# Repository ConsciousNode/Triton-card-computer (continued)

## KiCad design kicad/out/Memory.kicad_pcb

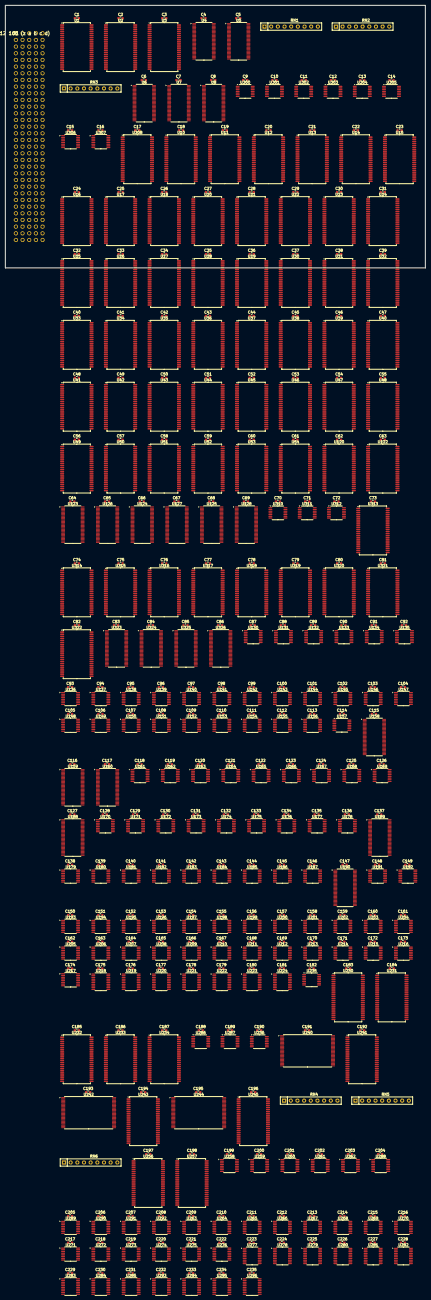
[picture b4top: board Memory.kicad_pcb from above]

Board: 4 copper layers, 160.0 x 100.0 mm, 477 parts (0 on the bottom side), 1061 nets, no tracks yet.

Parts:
C1, C2, C3, C4, C5, C6, C7, C8, C9, C10, C11, C12, C13, C14, C15, C16, C17, C18, C19, C20, C21, C22, C23, C24, C25, C26, C27, C28, C29, C30, C31, C32, C33, C34, C35, C36, C37, C38, C39, C40, C41, C42, C43, C44, C45, C46, C47, C48, C49, C50, C51, C52, C53, C54, C55, C56, C57, C58, C59, C60, C61, C62, C63, C64, C65, C66, C67, C68, C69, C70, C71, C72, C73, C74, C75, C76, C77, C78, C79, C80, C81, C82, C83, C84, C85, C86, C87, C88, C89, C90, C91, C92, C93, C94, C95, C96, C97, C98, C99, C100, C101, C102, C103, C104, C105, C106, C107, C108, C109, C110, C111, C112, C113, C114, C115, C116, C117, C118, C119, C120, C121, C122, C123, C124, C125, C126, C127, C128, C129, C130, C131, C132, C133, C134, C135, C136, C137, C138, C139, C140, C141, C142, C143, C144, C145, C146, C147, C148, C149, C150, C151, C152, C153, C154, C155, C156, C157, C158, C159, C160, C161, C162, C163, C164, C165, C166, C167, C168, C169, C170, C171, C172, C173, C174, C175, C176, C177, C178, C179, C180, C181, C182, C183, C184, C185, C186, C187, C188, C189, C190, C191, C192, C193, C194, C195, C196, C197, C198, C199, C200, C201, C202, C203, C204, C205, C206, C207, C208, C209, C210, C211, C212, C213, C214, C215, C216, C217, C218, C219, C220, C221, C222, C223, C224, C225, C226, C227, C228, C229, C230, C231, C232, C233, C234, C235: 100n; C_0603_1608Metric
J1: DIN41612 160 (z a b c d)
RN1, RN2, RN3: RPACK8; R_Array_SIP9
RN4, RN5, RN6: RPACK8G; R_Array_SIP9
U1, U2, U3, U10, U11, U12, U13, U14, U15, U16, U17, U18, U20, U21, U22, U23, U24, U25, U26, U27, U28, U29, U30, U31, U32, U33, U34, U35, U36, U37, U38, U39, U40, U41, U42, U43, U44, U45, U46, U47, U48, U49, U50, U51, U52, U53, U54, U120, U122, U230, U231, U232, U233, U234, U308, U313, U314, U315, U316, U317, U318, U319, U320, U321, U322: IS61WV5128; TSOP-II-44_10.16x18.41mm_P0.8mm
U4, U5, U6, U7, U8, U123, U124, U125, U126, U127, U128, U158, U159, U160, U188, U189, U190, U323, U324, U325, U326: ALVCH16823; TSSOP-56_6.1x14mm_P0.5mm
U130, U131, U132, U133, U134, U135, U136, U137, U138, U139, U140, U141, U142, U143, U144, U145, U146, U147, U148, U149, U150, U151, U152, U153, U154, U155, U156, U161, U162, U163, U164, U165, U166, U167, U168, U169, U170, U171, U172, U173, U174, U175, U176, U177, U178, U179, U180, U181, U182, U183, U184, U185, U186, U187, U268, U269, U270, U271, U272, U273, U274, U275, U276: LVC153; TSSOP-16_4.4x5mm_P0.65mm
U157, U235: LVC04; TSSOP-14_4.4x5mm_P0.65mm
U191, U192, U193, U194, U195, U196, U197, U198, U199, U200, U201, U202, U203, U204, U205, U206, U207, U208, U209, U210, U211, U212, U213, U214, U215, U216, U217: CBTLV3253; TSSOP-16_4.4x5mm_P0.65mm
U218, U219, U220, U221, U222, U223, U224, U277, U278, U279, U280, U281, U282, U283, U293, U294, U295, U296: LVC245; TSSOP-20_4.4x6.5mm_P0.65mm
U236, U287: LVC32; TSSOP-14_4.4x5mm_P0.65mm
U240, U242, U244: IS61WV204816; TSOP-I-48_18.4x12mm_P0.5mm
U241, U243, U245: IS61WV20488; TSOP-II-44_10.16x18.41mm_P0.8mm
U256, U257: IS61WV51216; TSOP-II-44_10.16x18.41mm_P0.8mm
U258, U259, U260, U261, U262: CBTLV3257; TSSOP-16_4.4x5mm_P0.65mm
U263, U264, U265, U266, U267, U288, U289, U290, U291, U292, U306, U307: LVC157; TSSOP-16_4.4x5mm_P0.65mm
U284, U285: LVC574; TSSOP-20_4.4x6.5mm_P0.65mm
U286: LVC08; TSSOP-14_4.4x5mm_P0.65mm
U300, U301, U302, U303, U304, U305, U310, U311, U312: LVC11; TSSOP-14_4.4x5mm_P0.65mm

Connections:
+3V3: C1.1, C2.1, C3.1, C4.1, C5.1, C6.1, C7.1, C8.1, C9.1, C10.1, C11.1, C12.1, C13.1, C14.1, C15.1, C16.1, C17.1, C18.1, C19.1, C20.1, C21.1, C22.1, C23.1, C24.1, C25.1, C26.1, C27.1, C28.1, C29.1, C30.1, C31.1, C32.1, C33.1, C34.1, C35.1, C36.1, C37.1, C38.1, C39.1, C40.1, C41.1, C42.1, C43.1, C44.1, C45.1, C46.1, C47.1, C48.1, C49.1, C50.1, C51.1, C52.1, C53.1, C54.1, C55.1, C56.1, C57.1, C58.1, C59.1, C60.1, C61.1, C62.1, C63.1, C64.1, C65.1, C66.1, C67.1, C68.1, C69.1, C70.1, C71.1, C72.1, C73.1, C74.1, C75.1, C76.1, C77.1, C78.1, C79.1, C80.1, C81.1, C82.1, C83.1, C84.1, C85.1, C86.1, C87.1, C88.1, C89.1, C90.1, C91.1, C92.1, C93.1, C94.1, C95.1, C96.1, C97.1, C98.1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
+5V: J1.z8, J1.z16, J1.z24, J1.z32
/CE0: U234.9, U240.7, U241.8
/CE1: U234.10, U242.7, U243.8
/CE2: U234.13, U244.7, U245.8
/FALD: U157.2, U158.30, U158.55, U159.30, U159.55, U160.30, U160.55
/RWE: U236.6, U240.18, U241.15, U242.18, U243.15, U244.18, U245.15
/SWR: U235.11, U286.2, U286.5, U293.19, U294.19, U295.19, U296.19
/UBLD: U122.9, U123.30, U123.55, U124.30, U124.55, U125.30, U125.55
/ULLD: U122.10, U126.30, U126.55, U127.30, U127.55, U128.30, U128.55, U323.30, U323.55, U324.30, U324.55, U325.30, U325.55, U326.30, U326.55
/VSWE: U257.17, U286.6
/VWE: U235.3, U236.8, U282.19, U283.19, U286.1, U286.4
/VXWE: U256.17, U286.3
/WA: U236.3, U236.9, U236.12
/WAS: U236.4, U236.11
/WSTB: J1.d1, U236.13
ABORT: J1.c15, U6.30, U6.55, U7.30, U7.55, U8.30, U8.55, U120.9, U122.18, U157.1, U188.30, U188.55, U189.30, U189.55, U190.30, U190.55, U236.2
BADADDR: J1.d2, U120.31
CLK: J1.c10, U4.29, U4.56, U5.29, U5.56, U6.29, U6.56, U7.29, U7.56, U8.29, U8.56, U123.29, U123.56, U124.29, U124.56, U125.29, U125.56, U126.29, U126.56, U127.29, U127.56, U128.29, U128.56, U158.29, U158.56, U159.29, U159.56, U160.29, U160.56, U188.29, U188.56, U189.29, U189.56, U190.29, U190.56, U323.29, U323.56, U324.29, U324.56, U325.29, U325.56, U326.29, U326.56
CSD0: U1.9, U4.54
CSD1: U1.10, U4.52
CSD2: U1.13, U4.51
CSD3: U1.14, U4.49
CSD4: U1.31, U4.48
CSD5: U1.32, U4.47
CSD6: U1.35, U4.45
CSD7: U1.36, U4.44
CSD8: U2.9, U4.43
CSD9: U2.10, U4.42
CSD10: U2.13, U4.41
CSD11: U2.14, U4.40
CSD12: U2.31, U4.38
CSD13: U2.32, U4.37
CSD14: U2.35, U4.36
CSD15: U2.36, U4.34
CSD16: U3.9, U4.33
CSD17: U3.10, U4.31
CSD18: U3.13, U5.54
CSD19: U3.14, U5.52
CSD20: U3.31, U5.51
CSD21: U3.32, U5.49
CW_/MBUSOE: RN3.3, U4.26, U218.19, U219.19, U220.19, U221.19, U222.19, U223.19, U224.19
CW_/MWR: RN3.5, U5.5, U235.1, U236.1, U277.19, U278.19, U279.19, U280.19, U281.19
CW_BS0_0: RN2.5, U4.17, U191.14, U192.14, U193.14, U194.14, U195.14, U196.14, U197.14, U198.14, U199.14
CW_BS0_1: RN2.6, U4.19, U191.2, U192.2, U193.2, U194.2, U195.2, U196.2, U197.2, U198.2, U199.2
CW_BS1_0: RN2.7, U4.20, U200.14, U201.14, U202.14, U203.14, U204.14, U205.14, U206.14, U207.14, U208.14
CW_BS1_1: RN2.8, U4.21, U200.2, U201.2, U202.2, U203.2, U204.2, U205.2, U206.2, U207.2, U208.2
CW_BS2_0: RN2.9, U4.23, U209.14, U210.14, U211.14, U212.14, U213.14, U214.14, U215.14, U216.14, U217.14
CW_BS2_1: RN3.2, U4.24, U209.2, U210.2, U211.2, U212.2, U213.2, U214.2, U215.2, U216.2, U217.2
CW_MARC: RN1.4, U4.6, U10.28, U308.19
CW_MK0: RN2.3, U4.15, U120.6
CW_MK1: RN2.4, U4.16, U120.7
CW_MOP0: RN1.2, U4.3, U10.29, U11.29, U12.29, U13.29, U14.29, U15.29, U16.29, U17.29, U18.29
CW_MOP1: RN1.3, U4.5, U10.30, U11.30, U12.30, U13.30, U14.30, U15.30, U16.30, U17.30, U18.30, U306.1, U307.1
CW_MS0_0: RN1.5, U4.8, U161.14, U162.14, U163.14, U164.14, U165.14, U166.14, U167.14, U168.14, U169.14
CW_MS0_1: RN1.6, U4.9, U161.2, U162.2, U163.2, U164.2, U165.2, U166.2, U167.2, U168.2, U169.2
CW_MS1_0: RN1.7, U4.10, U170.14, U171.14, U172.14, U173.14, U174.14, U175.14, U176.14, U177.14, U178.14
CW_MS1_1: RN1.8, U4.12, U170.2, U171.2, U172.2, U173.2, U174.2, U175.2, U176.2, U177.2, U178.2
CW_MS2_0: RN1.9, U4.13, U179.14, U180.14, U181.14, U182.14, U183.14, U184.14, U185.14, U186.14, U187.14
CW_MS2_1: RN2.2, U4.14, U179.2, U180.2, U181.2, U182.2, U183.2, U184.2, U185.2, U186.2, U187.2
CW_RFWR: RN3.4, U5.3, U122.16
CW_WL0: RN3.6, U5.6, U268.14, U269.14, U270.14, U271.14, U272.14, U273.14, U274.14, U275.14, U276.14
CW_WL1: RN3.7, U5.8, U268.2, U269.2, U270.2, U271.2, U272.2, U273.2, U274.2, U275.2, U276.2
D0+: J1.a1, U10.17, U123.54, U126.54, U161.4, U161.5, U170.4, U179.4, U218.18, U302.9, U313.3, U314.3
D0-: J1.a2, U10.18, U123.52, U126.52, U161.11, U161.12, U170.12, U179.12, U218.17, U313.4, U314.4
D1+: J1.a3, U10.19, U123.51, U126.51, U162.4, U162.5, U171.4, U180.4, U218.16, U302.10, U313.5, U314.5
D1-: J1.a4, U10.20, U123.49, U126.49, U162.11, U162.12, U171.12, U180.12, U218.15, U313.6, U314.6
D2+: J1.a5, U10.26, U123.48, U126.48, U163.4, U163.5, U172.4, U181.4, U218.14, U302.11, U313.7, U314.7
D2-: J1.a6, U10.27, U123.47, U126.47, U163.11, U163.12, U172.12, U181.12, U218.13, U313.16, U314.16
D3+: J1.a7, U11.17, U123.45, U126.45, U164.4, U164.5, U173.4, U182.4, U218.12, U303.1, U315.3
D3-: J1.a9, U11.18, U123.44, U126.44, U164.11, U164.12, U173.12, U182.12, U218.11, U310.1, U315.4
D4+: J1.a10, U11.19, U123.43, U126.43, U165.4, U165.5, U174.4, U183.4, U219.18, U303.2, U315.5
D4-: J1.a11, U11.20, U123.42, U126.42, U165.11, U165.12, U174.12, U183.12, U219.17, U310.2, U315.6
D5+: J1.a12, U11.26, U123.41, U126.41, U166.4, U166.5, U175.4, U184.4, U219.16, U303.13, U315.7
D5-: J1.a13, U11.27, U123.40, U126.40, U166.11, U166.12, U175.12, U184.12, U219.15, U310.13, U315.16
D6+: J1.a14, U12.17, U123.38, U126.38, U167.4, U167.5, U176.4, U185.4, U219.14, U303.3, U316.3
D6-: J1.a15, U12.18, U123.37, U126.37, U167.11, U167.12, U176.12, U185.12, U219.13, U310.3, U316.4
D7+: J1.a17, U12.19, U123.36, U126.36, U168.4, U168.5, U177.4, U186.4, U219.12, U303.4, U316.5
D7-: J1.a18, U12.20, U123.34, U126.34, U168.11, U168.12, U177.12, U186.12, U219.11, U310.4, U316.6
D8+: J1.a19, U12.26, U123.33, U126.33, U169.4, U169.5, U178.4, U187.4, U220.18, U303.5, U316.7
D8-: J1.a20, U12.27, U123.31, U126.31, U169.11, U169.12, U178.12, U187.12, U220.17, U310.5, U316.16
D9+: J1.a21, U13.17, U124.54, U127.54, U170.5, U220.16, U303.9, U317.3
D9-: J1.a22, U13.18, U124.52, U127.52, U170.11, U220.15, U310.9, U317.4
D10+: J1.a23, U13.19, U124.51, U127.51, U171.5, U220.14, U303.10, U317.5
D10-: J1.a25, U13.20, U124.49, U127.49, U171.11, U220.13, U310.10, U317.6
D11+: J1.a26, U13.26, U124.48, U127.48, U172.5, U220.12, U303.11, U317.7
D11-: J1.a27, U13.27, U124.47, U127.47, U172.11, U220.11, U310.11, U317.16
D12+: J1.a28, U14.17, U124.45, U127.45, U173.5, U221.18, U304.1, U318.3
D12-: J1.a29, U14.18, U124.44, U127.44, U173.11, U221.17, U311.1, U318.4
D13+: J1.a30, U14.19, U124.43, U127.43, U174.5, U221.16, U304.2, U318.5
D13-: J1.a31, U14.20, U124.42, U127.42, U174.11, U221.15, U311.2, U318.6
D14+: J1.b1, U14.26, U124.41, U127.41, U175.5, U221.14, U304.13, U318.7
D14-: J1.b2, U14.27, U124.40, U127.40, U175.11, U221.13, U311.13, U318.16
D15+: J1.b3, U15.17, U124.38, U127.38, U176.5, U221.12, U304.3, U319.3
D15-: J1.b4, U15.18, U124.37, U127.37, U176.11, U221.11, U311.3, U319.4
D16+: J1.b5, U15.19, U124.36, U127.36, U177.5, U222.18, U304.4, U319.5
D16-: J1.b6, U15.20, U124.34, U127.34, U177.11, U222.17, U311.4, U319.6
D17+: J1.b7, U15.26, U124.33, U127.33, U178.5, U222.16, U304.5, U319.7
D17-: J1.b9, U15.27, U124.31, U127.31, U178.11, U222.15, U311.5, U319.16
D18+: J1.b10, U16.17, U125.54, U128.54, U179.5, U222.14, U304.9, U320.3
D18-: J1.b11, U16.18, U125.52, U128.52, U179.11, U222.13, U311.9, U320.4
D19+: J1.b12, U16.19, U125.51, U128.51, U180.5, U222.12, U304.10, U320.5
D19-: J1.b13, U16.20, U125.49, U128.49, U180.11, U222.11, U311.10, U320.6
D20+: J1.b14, U16.26, U125.48, U128.48, U181.5, U223.18, U304.11, U320.7
D20-: J1.b15, U16.27, U125.47, U128.47, U181.11, U223.17, U311.11, U320.16
D21+: J1.b17, U17.17, U125.45, U128.45, U182.5, U223.16, U305.1, U321.3
D21-: J1.b18, U17.18, U125.44, U128.44, U182.11, U223.15, U312.1, U321.4
D22+: J1.b19, U17.19, U125.43, U128.43, U183.5, U223.14, U305.2, U321.5
D22-: J1.b20, U17.20, U125.42, U128.42, U183.11, U223.13, U312.2, U321.6
D23+: J1.b21, U17.26, U125.41, U128.41, U184.5, U223.12, U305.13, U321.7
D23-: J1.b22, U17.27, U125.40, U128.40, U184.11, U223.11, U312.13, U321.16
D24+: J1.b23, U18.17, U125.38, U128.38, U185.5, U224.18, U322.3
D24-: J1.b25, U18.18, U125.37, U128.37, U185.11, U224.17, U312.3, U322.4
D25+: J1.b26, U18.19, U125.36, U128.36, U186.5, U224.16, U322.5
D25-: J1.b27, U18.20, U125.34, U128.34, U186.11, U224.15, U312.4, U322.6
D26+: J1.b28, U18.26, U125.33, U128.33, U187.5, U224.14, U322.7
D26-: J1.b29, U18.27, U125.31, U128.31, U187.11, U224.13, U312.5, U322.16
DB1: U313.9, U315.17
DB2: U313.10, U316.17
DB3: U313.13, U317.17
DB4: U313.14, U318.17
DB5: U313.31, U319.17
DB6: U313.32, U320.17
DB7: U313.35, U321.17
DB8: U312.9, U313.36, U322.17
DM0+: U314.9, U323.54
DM0-: U314.10, U323.52
DM1+: U314.13, U323.51
DM1-: U314.14, U323.49
DM2+: U314.31, U323.48
DM2-: U314.32, U323.47
DM3+: U315.9, U323.45
DM3-: U315.10, U323.44
DM4+: U315.13, U323.43
DM4-: U315.14, U323.42
DM5+: U315.31, U323.41
DM5-: U315.32, U323.40
DM6+: U316.9, U323.38
DM6-: U316.10, U323.37
DM7+: U316.13, U323.36
DM7-: U316.14, U323.34
DM8+: U316.31, U323.33
DM8-: U316.32, U323.31
DM9+: U317.9, U324.54
DM9-: U317.10, U324.52
DM10+: U317.13, U324.51
DM10-: U317.14, U324.49
DM11+: U317.31, U324.48
DM11-: U317.32, U324.47
DM12+: U318.9, U324.45
DM12-: U318.10, U324.44
DM13+: U318.13, U324.43
DM13-: U318.14, U324.42
DM14+: U318.31, U324.41
DM14-: U318.32, U324.40
DM15+: U319.9, U324.38
DM15-: U319.10, U324.37
DM16+: U319.13, U324.36
DM16-: U319.14, U324.34
DM17+: U319.31, U324.33
DM17-: U319.32, U324.31
DM18+: U320.9, U325.54
DM18-: U320.10, U325.52
DM19+: U320.13, U325.51
DM19-: U320.14, U325.49
DM20+: U320.31, U325.48
DM20-: U320.32, U325.47
DM21+: U321.9, U325.45
DM21-: U321.10, U325.44
DM22+: U321.13, U325.43
DM22-: U321.14, U325.42
DM23+: U321.31, U325.41
DM23-: U321.32, U325.40
DM24+: U322.9, U325.38
DM24-: U322.10, U325.37
DM25+: U322.13, U325.36
DM25-: U322.14, U325.34
DM26+: U322.31, U325.33
DM26-: U322.32, U325.31
DN1: U310.12, U313.17
DN2: U310.6, U313.18
DN3: U310.8, U313.19
DN4: U311.12, U313.20
DN5: U311.6, U313.26
DN6: U311.8, U313.27
DN7: U312.12, U313.28
DN8: U312.6, U312.10
ES0: U120.13, U130.14, U131.14, U132.14, U133.14, U134.14, U135.14, U136.14, U137.14, U138.14, U139.14, U140.14, U141.14, U142.14, U143.14, U144.14, U145.14, U146.14, U147.14, U148.14, U149.14, U150.14, U151.14, U152.14, U153.14, U154.14, U155.14, U156.14
ES1: U120.14, U130.2, U131.2, U132.2, U133.2, U134.2, U135.2, U136.2, U137.2, U138.2, U139.2, U140.2, U141.2, U142.2, U143.2, U144.2, U145.2, U146.2, U147.2, U148.2, U149.2, U150.2, U151.2, U152.2, U153.2, U154.2, U155.2, U156.2
FA0+: U158.3, U191.4
FA0-: U158.5, U191.12
FA1+: U158.6, U192.4
FA1-: U158.8, U192.12
FA2+: U158.9, U193.4
FA2-: U158.10, U193.12
FA3+: U158.12, U194.4
FA3-: U158.13, U194.12
FA4+: U158.14, U195.4
FA4-: U158.15, U195.12
FA5+: U158.16, U196.4
FA5-: U158.17, U196.12
FA6+: U158.19, U197.4
FA6-: U158.20, U197.12
FA7+: U158.21, U198.4
FA7-: U158.23, U198.12
FA8+: U158.24, U199.4
FA8-: U158.26, U199.12
FA9+: U159.3, U200.4
FA9-: U159.5, U200.12
FA10+: U159.6, U201.4
FA10-: U159.8, U201.12
FA11+: U159.9, U202.4
FA11-: U159.10, U202.12
FA12+: U159.12, U203.4
FA12-: U159.13, U203.12
FA13+: U159.14, U204.4
FA13-: U159.15, U204.12
FA14+: U159.16, U205.4
FA14-: U159.17, U205.12
FA15+: U159.19, U206.4
FA15-: U159.20, U206.12
FA16+: U159.21, U207.4
FA16-: U159.23, U207.12
FA17+: U159.24, U208.4
FA17-: U159.26, U208.12
FA18+: U160.3, U209.4
FA18-: U160.5, U209.12
FA19+: U160.6, U210.4
FA19-: U160.8, U210.12
FA20+: U160.9, U211.4
FA20-: U160.10, U211.12
FA21+: U160.12, U212.4
FA21-: U160.13, U212.12
FA22+: U160.14, U213.4
FA22-: U160.15, U213.12
FA23+: U160.16, U214.4
FA23-: U160.17, U214.12
FA24+: U160.19, U215.4
FA24-: U160.20, U215.12
FA25+: U160.21, U216.4
FA25-: U160.23, U216.12
FA26+: U160.24, U217.4
FA26-: U160.26, U217.12
FBN: U235.6, U236.10
FBSEL: U233.32, U235.5, U236.5, U263.1, U264.1, U265.1, U266.1, U267.1
FK: J1.c17, U120.10
FN0+: U130.7, U158.54
FN0-: U130.9, U158.52
FN1+: U131.7, U158.51
FN1-: U131.9, U158.49
FN2+: U132.7, U158.48
FN2-: U132.9, U158.47
FN3+: U133.7, U158.45
FN3-: U133.9, U158.44
FN4+: U134.7, U158.43
FN4-: U134.9, U158.42
FN5+: U135.7, U158.41
FN5-: U135.9, U158.40
FN6+: U136.7, U158.38
FN6-: U136.9, U158.37
FN7+: U137.7, U158.36
FN7-: U137.9, U158.34
FN8+: U138.7, U158.33
FN8-: U138.9, U158.31
FN9+: U139.7, U159.54
FN9-: U139.9, U159.52
FN10+: U140.7, U159.51
FN10-: U140.9, U159.49
FN11+: U141.7, U159.48
FN11-: U141.9, U159.47
FN12+: U142.7, U159.45
FN12-: U142.9, U159.44
FN13+: U143.7, U159.43
FN13-: U143.9, U159.42
FN14+: U144.7, U159.41
FN14-: U144.9, U159.40
FN15+: U145.7, U159.38
FN15-: U145.9, U159.37
FN16+: U146.7, U159.36
FN16-: U146.9, U159.34
FN17+: U147.7, U159.33
FN17-: U147.9, U159.31
FN18+: U148.7, U160.54
FN18-: U148.9, U160.52
FN19+: U149.7, U160.51
FN19-: U149.9, U160.49
FN20+: U150.7, U160.48
FN20-: U150.9, U160.47
FN21+: U151.7, U160.45
FN21-: U151.9, U160.44
FN22+: U152.7, U160.43
FN22-: U152.9, U160.42
FN23+: U153.7, U160.41
FN23-: U153.9, U160.40
FN24+: U154.7, U160.38
FN24-: U154.9, U160.37
FN25+: U155.7, U160.36
FN25-: U155.9, U160.34
FN26+: U156.7, U160.33
FN26-: U156.9, U160.31
GND: C1.2, C2.2, C3.2, C4.2, C5.2, C6.2, C7.2, C8.2, C9.2, C10.2, C11.2, C12.2, C13.2, C14.2, C15.2, C16.2, C17.2, C18.2, C19.2, C20.2, C21.2, C22.2, C23.2, C24.2, C25.2, C26.2, C27.2, C28.2, C29.2, C30.2, C31.2, C32.2, C33.2, C34.2, C35.2, C36.2, C37.2, C38.2, C39.2, C40.2, C41.2, C42.2, C43.2, C44.2, C45.2, C46.2, C47.2, C48.2, C49.2, C50.2, C51.2, C52.2, C53.2, C54.2, C55.2, C56.2, C57.2, C58.2, C59.2, C60.2, C61.2, C62.2, C63.2, C64.2, C65.2, C66.2, C67.2, C68.2, C69.2, C70.2, C71.2, C72.2, C73.2, C74.2, C75.2, C76.2, C77.2, C78.2, C79.2, C80.2, C81.2, C82.2, C83.2, C84.2, C85.2, C86.2, C87.2, C88.2, C89.2, C90.2, C91.2, C92.2, C93.2, C94.2, C95.2, C96.2, C97.2, C98.2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
K4_0+: U44.9, U52.3
K4_0-: U44.10, U52.4
K4_1+: U46.9, U52.5
K4_1-: U46.10, U52.6
K4_2+: U48.9, U52.7
K4_2-: U48.10, U52.16
K4_3+: U50.9, U52.17
K4_3-: U50.10, U52.18
K5_0+: U44.13, U52.19
K5_0-: U44.14, U52.20
K5_1+: U46.13, U52.26
K5_1-: U46.14, U52.27
K5_2+: U48.13, U52.28
K5_2-: U48.14, U52.29
K5_3+: U50.13, U52.30
K5_3-: U50.14, U52.38
K6_0+: U44.31, U53.3
K6_0-: U44.32, U53.4
K6_1+: U46.31, U53.5
K6_1-: U46.32, U53.6
K6_2+: U48.31, U53.7
K6_2-: U48.32, U53.16
K6_3+: U50.31, U53.17
K6_3-: U50.32, U53.18
K7_0+: U44.35, U53.19
K7_0-: U44.36, U53.20
K7_1+: U46.35, U53.26
K7_1-: U46.36, U53.27
K7_2+: U48.35, U53.28
K7_2-: U48.36, U53.29
K7_3+: U50.35, U53.30
K7_3-: U50.36, U53.38
K8_0+: U45.9, U54.3
K8_0-: U45.10, U54.4
K8_1+: U47.9, U54.5
K8_1-: U47.10, U54.6
K8_2+: U49.9, U54.7
K8_2-: U49.10, U54.16
K8_3+: U51.9, U54.17
K8_3-: U51.10, U54.18
K9_0+: U45.13, U54.19
K9_0-: U45.14, U54.20
K9_1+: U47.13, U54.26
K9_1-: U47.14, U54.27
K9_2+: U49.13, U54.28
K9_2-: U49.14, U54.29
K9_3+: U51.13, U54.30
K9_3-: U51.14, U54.38
MAR0+: U6.3, U10.3, U20.3, U28.3, U36.3, U44.3, U45.3, U130.6, U191.6, U230.3, U232.3, U300.1
MAR0-: U6.5, U10.4, U20.4, U28.4, U36.4, U44.4, U45.4, U130.10, U191.10, U230.4, U232.4
MAR1+: U6.6, U10.5, U20.5, U28.5, U36.5, U44.5, U45.5, U131.6, U192.6, U230.5, U232.5, U300.2
MAR1-: U6.8, U10.6, U20.6, U28.6, U36.6, U44.6, U45.6, U131.10, U192.10, U230.6, U232.6
MAR2+: U6.9, U10.7, U20.7, U28.7, U36.7, U44.7, U45.7, U132.6, U193.6, U230.7, U232.7, U300.13
MAR2-: U6.10, U10.16, U20.16, U28.16, U36.16, U44.16, U45.16, U132.10, U193.10, U230.16, U232.16
MAR3+: U6.12, U11.3, U20.17, U28.17, U36.17, U44.17, U45.17, U133.6, U194.6, U230.17, U232.17, U300.3
MAR3-: U6.13, U11.4, U20.18, U28.18, U36.18, U44.18, U45.18, U133.10, U194.10, U230.18, U232.18
MAR4+: U6.14, U11.5, U21.3, U29.3, U37.3, U44.19, U45.19, U134.6, U195.6, U230.19, U232.19, U300.4
MAR4-: U6.15, U11.6, U21.4, U29.4, U37.4, U44.20, U45.20, U134.10, U195.10, U230.20, U232.20
MAR5+: U6.16, U11.7, U21.5, U29.5, U37.5, U44.26, U45.26, U135.6, U196.6, U231.3, U232.26, U300.5
MAR5-: U6.17, U11.16, U21.6, U29.6, U37.6, U44.27, U45.27, U135.10, U196.10, U231.4, U232.27
MAR6+: U6.19, U12.3, U21.7, U29.7, U37.7, U44.28, U45.28, U136.6, U197.6, U231.5, U232.28, U300.9
MAR6-: U6.20, U12.4, U21.16, U29.16, U37.16, U44.29, U45.29, U136.10, U197.10, U231.6, U232.29
MAR7+: U6.21, U12.5, U21.17, U29.17, U37.17, U46.3, U47.3, U137.6, U198.6, U231.7, U232.30, U300.10
MAR7-: U6.23, U12.6, U21.18, U29.18, U37.18, U46.4, U47.4, U137.10, U198.10, U231.16, U232.38
MAR8+: U6.24, U12.7, U22.3, U30.3, U38.3, U46.5, U47.5, U138.6, U199.6, U231.17, U232.39, U300.11
MAR8-: U6.26, U12.16, U22.4, U30.4, U38.4, U46.6, U47.6, U138.10, U199.10, U231.18, U232.40
MAR9+: U7.3, U13.3, U22.5, U30.5, U38.5, U46.7, U47.7, U139.6, U200.6, U231.19, U301.1
MAR9-: U7.5, U13.4, U22.6, U30.6, U38.6, U46.16, U47.16, U139.10, U200.10, U231.20
MAR10+: U7.6, U13.5, U22.7, U30.7, U38.7, U46.17, U47.17, U140.6, U201.6, U233.3, U234.3, U301.2
MAR10-: U7.8, U13.6, U22.16, U30.16, U38.16, U46.18, U47.18, U140.10, U201.10, U233.4, U234.4
MAR11+: U7.9, U13.7, U22.17, U30.17, U38.17, U46.19, U47.19, U141.6, U202.6, U233.5, U234.5, U301.13
MAR11-: U7.10, U13.16, U22.18, U30.18, U38.18, U46.20, U47.20, U141.10, U202.10, U233.6, U234.6
MAR12+: U7.12, U14.3, U23.3, U31.3, U39.3, U46.26, U47.26, U142.6, U203.6, U233.7, U234.7, U301.3
MAR12-: U7.13, U14.4, U23.4, U31.4, U39.4, U46.27, U47.27, U142.10, U203.10, U233.16, U234.16
MAR13+: U7.14, U14.5, U23.5, U31.5, U39.5, U46.28, U47.28, U143.6, U204.6, U233.17, U234.17, U301.4
MAR13-: U7.15, U14.6, U23.6, U31.6, U39.6, U46.29, U47.29, U143.10, U204.10, U233.18, U234.18
MAR14+: U7.16, U14.7, U23.7, U31.7, U39.7, U48.3, U49.3, U144.6, U205.6, U233.19, U234.19, U301.5
MAR14-: U7.17, U14.16, U23.16, U31.16, U39.16, U48.4, U49.4, U144.10, U205.10, U233.20, U234.20
MAR15+: U7.19, U15.3, U23.17, U31.17, U39.17, U48.5, U49.5, U145.6, U206.6, U233.26, U234.26, U301.9
MAR15-: U7.20, U15.4, U23.18, U31.18, U39.18, U48.6, U49.6, U145.10, U206.10, U233.27, U234.27
MAR16+: U7.21, U15.5, U24.3, U32.3, U40.3, U48.7, U49.7, U146.6, U207.6, U301.10
MAR16-: U7.23, U15.6, U24.4, U32.4, U40.4, U48.16, U49.16, U146.10, U207.10
MAR17+: U7.24, U15.7, U24.5, U32.5, U40.5, U48.17, U49.17, U147.6, U208.6, U301.11
MAR17-: U7.26, U15.16, U24.6, U32.6, U40.6, U48.18, U49.18, U147.10, U208.10
MAR18+: U8.3, U16.3, U24.7, U32.7, U40.7, U48.19, U49.19, U148.6, U209.6, U302.1
MAR18-: U8.5, U16.4, U24.16, U32.16, U40.16, U48.20, U49.20, U148.10, U209.10
MAR19+: U8.6, U16.5, U24.17, U32.17, U40.17, U48.26, U49.26, U149.6, U210.6, U302.2
MAR19-: U8.8, U16.6, U24.18, U32.18, U40.18, U48.27, U49.27, U149.10, U210.10
MAR20+: U8.9, U16.7, U25.3, U33.3, U41.3, U48.28, U49.28, U150.6, U211.6, U302.13
MAR20-: U8.10, U16.16, U25.4, U33.4, U41.4, U48.29, U49.29, U150.10, U211.10
MAR21+: U8.12, U17.3, U25.5, U33.5, U41.5, U50.3, U51.3, U151.6, U212.6, U302.3
MAR21-: U8.13, U17.4, U25.6, U33.6, U41.6, U50.4, U51.4, U151.10, U212.10
MAR22+: U8.14, U17.5, U25.7, U33.7, U41.7, U50.5, U51.5, U152.6, U213.6, U302.4
MAR22-: U8.15, U17.6, U25.16, U33.16, U41.16, U50.6, U51.6, U152.10, U213.10
MAR23+: U8.16, U17.7, U25.17, U33.17, U41.17, U50.7, U51.7, U153.6, U214.6, U302.5
MAR23-: U8.17, U17.16, U25.18, U33.18, U41.18, U50.16, U51.16, U153.10, U214.10
MAR24+: U8.19, U18.3, U26.3, U34.3, U42.3, U50.17, U51.17, U154.6, U215.6
MAR24-: U8.20, U18.4, U26.4, U34.4, U42.4, U50.18, U51.18, U154.10, U215.10
MAR25+: U8.21, U18.5, U26.5, U34.5, U42.5, U50.19, U51.19, U155.6, U216.6
MAR25-: U8.23, U18.6, U26.6, U34.6, U42.6, U50.20, U51.20, U155.10, U216.10
MAR26+: U8.24, U18.7, U26.7, U34.7, U42.7, U50.26, U51.26, U156.6, U217.6
MAR26-: U8.26, U18.16, U26.16, U34.16, U42.16, U50.27, U51.27, U156.10, U217.10
MB0+: U191.7, U218.2
MB0-: U191.9, U218.3
MB1+: U192.7, U218.4
MB1-: U192.9, U218.5
MB2+: U193.7, U218.6
MB2-: U193.9, U218.7
MB3+: U194.7, U218.8
MB3-: U194.9, U218.9
MB4+: U195.7, U219.2
MB4-: U195.9, U219.3
MB5+: U196.7, U219.4
MB5-: U196.9, U219.5
MB6+: U197.7, U219.6
MB6-: U197.9, U219.7
MB7+: U198.7, U219.8
MB7-: U198.9, U219.9
MB8+: U199.7, U220.2
MB8-: U199.9, U220.3
MB9+: U200.7, U220.4
MB9-: U200.9, U220.5
MB10+: U201.7, U220.6
MB10-: U201.9, U220.7
MB11+: U202.7, U220.8
MB11-: U202.9, U220.9
MB12+: U203.7, U221.2
MB12-: U203.9, U221.3
MB13+: U204.7, U221.4
MB13-: U204.9, U221.5
MB14+: U205.7, U221.6
MB14-: U205.9, U221.7
MB15+: U206.7, U221.8
MB15-: U206.9, U221.9
MB16+: U207.7, U222.2
MB16-: U207.9, U222.3
MB17+: U208.7, U222.4
MB17-: U208.9, U222.5
MB18+: U209.7, U222.6
MB18-: U209.9, U222.7
MB19+: U210.7, U222.8
MB19-: U210.9, U222.9
MB20+: U211.7, U223.2
MB20-: U211.9, U223.3
MB21+: U212.7, U223.4
MB21-: U212.9, U223.5
MB22+: U213.7, U223.6
MB22-: U213.9, U223.7
MB23+: U214.7, U223.8
MB23-: U214.9, U223.9
MB24+: U215.7, U224.2
MB24-: U215.9, U224.3
MB25+: U216.7, U224.4
MB25-: U216.9, U224.5
MB26+: U217.7, U224.6
MB26-: U217.9, U224.7
MC1: U11.28, U308.9
MC2: U12.28, U308.10
MC3: U13.28, U308.13
MC4: U14.28, U308.14
MC5: U15.28, U308.31
MC6: U16.28, U308.32
MC7: U17.28, U308.35
MC8: U18.28, U308.36
MDN0+: U161.7, U188.54
MDN0-: U161.9, U188.52
MDN1+: U162.7, U188.51
MDN1-: U162.9, U188.49
MDN2+: U163.7, U188.48
MDN2-: U163.9, U188.47
MDN3+: U164.7, U188.45
MDN3-: U164.9, U188.44
MDN4+: U165.7, U188.43
MDN4-: U165.9, U188.42
MDN5+: U166.7, U188.41
MDN5-: U166.9, U188.40
MDN6+: U167.7, U188.38
MDN6-: U167.9, U188.37
MDN7+: U168.7, U188.36
MDN7-: U168.9, U188.34
MDN8+: U169.7, U188.33
MDN8-: U169.9, U188.31
MDN9+: U170.7, U189.54
MDN9-: U170.9, U189.52
MDN10+: U171.7, U189.51
MDN10-: U171.9, U189.49
MDN11+: U172.7, U189.48
MDN11-: U172.9, U189.47
MDN12+: U173.7, U189.45
MDN12-: U173.9, U189.44
MDN13+: U174.7, U189.43
MDN13-: U174.9, U189.42
MDN14+: U175.7, U189.41
MDN14-: U175.9, U189.40
MDN15+: U176.7, U189.38
MDN15-: U176.9, U189.37
MDN16+: U177.7, U189.36
MDN16-: U177.9, U189.34
MDN17+: U178.7, U189.33
MDN17-: U178.9, U189.31
MDN18+: U179.7, U190.54
MDN18-: U179.9, U190.52
MDN19+: U180.7, U190.51
MDN19-: U180.9, U190.49
MDN20+: U181.7, U190.48
MDN20-: U181.9, U190.47
MDN21+: U182.7, U190.45
MDN21-: U182.9, U190.44
MDN22+: U183.7, U190.43
MDN22-: U183.9, U190.42
MDN23+: U184.7, U190.41
MDN23-: U184.9, U190.40
MDN24+: U185.7, U190.38
MDN24-: U185.9, U190.37
MDN25+: U186.7, U190.36
MDN25-: U186.9, U190.34
MDN26+: U187.7, U190.33
MDN26-: U187.9, U190.31
MDR0+: U161.6, U188.3, U191.5, U268.6
MDR0-: U161.10, U188.5, U191.11, U268.10
MDR1+: U162.6, U188.6, U192.5, U269.6
MDR1-: U162.10, U188.8, U192.11, U269.10
MDR2+: U163.6, U188.9, U193.5, U270.6
MDR2-: U163.10, U188.10, U193.11, U270.10
MDR3+: U164.6, U188.12, U194.5, U271.6
MDR3-: U164.10, U188.13, U194.11, U271.10
MDR4+: U165.6, U188.14, U195.5, U272.6
MDR4-: U165.10, U188.15, U195.11, U272.10
MDR5+: U166.6, U188.16, U196.5, U273.6
MDR5-: U166.10, U188.17, U196.11, U273.10
MDR6+: U167.6, U188.19, U197.5, U274.6
MDR6-: U167.10, U188.20, U197.11, U274.10
MDR7+: U168.6, U188.21, U198.5, U275.6
MDR7-: U168.10, U188.23, U198.11, U275.10
MDR8+: U169.6, U188.24, U199.5, U276.6
MDR8-: U169.10, U188.26, U199.11, U276.10
MDR9+: U170.6, U189.3, U200.5, U268.5
MDR9-: U170.10, U189.5, U200.11, U268.11
MDR10+: U171.6, U189.6, U201.5, U269.5
MDR10-: U171.10, U189.8, U201.11, U269.11
MDR11+: U172.6, U189.9, U202.5, U270.5
MDR11-: U172.10, U189.10, U202.11, U270.11
MDR12+: U173.6, U189.12, U203.5, U271.5
MDR12-: U173.10, U189.13, U203.11, U271.11
MDR13+: U174.6, U189.14, U204.5, U272.5
MDR13-: U174.10, U189.15, U204.11, U272.11
MDR14+: U175.6, U189.16, U205.5, U273.5
MDR14-: U175.10, U189.17, U205.11, U273.11
MDR15+: U176.6, U189.19, U206.5, U274.5
MDR15-: U176.10, U189.20, U206.11, U274.11
MDR16+: U177.6, U189.21, U207.5, U275.5
MDR16-: U177.10, U189.23, U207.11, U275.11
MDR17+: U178.6, U189.24, U208.5, U276.5
MDR17-: U178.10, U189.26, U208.11, U276.11
MDR18+: U179.6, U190.3, U209.5, U268.4
MDR18-: U179.10, U190.5, U209.11, U268.12
MDR19+: U180.6, U190.6, U210.5, U269.4
MDR19-: U180.10, U190.8, U210.11, U269.12
MDR20+: U181.6, U190.9, U211.5, U270.4
MDR20-: U181.10, U190.10, U211.11, U270.12
MDR21+: U182.6, U190.12, U212.5, U271.4
MDR21-: U182.10, U190.13, U212.11, U271.12
MDR22+: U183.6, U190.14, U213.5, U272.4
MDR22-: U183.10, U190.15, U213.11, U272.12
MDR23+: U184.6, U190.16, U214.5, U273.4
MDR23-: U184.10, U190.17, U214.11, U273.12
MDR24+: U185.6, U190.19, U215.5, U274.4
MDR24-: U185.10, U190.20, U215.11, U274.12
MDR25+: U186.6, U190.21, U216.5, U275.4
MDR25-: U186.10, U190.23, U216.11, U275.12
MDR26+: U187.6, U190.24, U217.5, U276.4
MDR26-: U187.10, U190.26, U217.11, U276.12
MN0+: U6.54, U10.9
MN0-: U6.52, U10.10
MN1+: U6.51, U10.13
MN1-: U6.49, U10.14
MN2+: U6.48, U10.31
MN2-: U6.47, U10.32
MN3+: U6.45, U11.9
MN3-: U6.44, U11.10
MN4+: U6.43, U11.13
MN4-: U6.42, U11.14
MN5+: U6.41, U11.31
MN5-: U6.40, U11.32
MN6+: U6.38, U12.9
MN6-: U6.37, U12.10
MN7+: U6.36, U12.13
MN7-: U6.34, U12.14
MN8+: U6.33, U12.31
MN8-: U6.31, U12.32
MN9+: U7.54, U13.9
MN9-: U7.52, U13.10
MN10+: U7.51, U13.13
MN10-: U7.49, U13.14
MN11+: U7.48, U13.31
MN11-: U7.47, U13.32
MN12+: U7.45, U14.9
MN12-: U7.44, U14.10
MN13+: U7.43, U14.13
MN13-: U7.42, U14.14
MN14+: U7.41, U14.31
MN14-: U7.40, U14.32
MN15+: U7.38, U15.9
MN15-: U7.37, U15.10
MN16+: U7.36, U15.13
MN16-: U7.34, U15.14
MN17+: U7.33, U15.31
MN17-: U7.31, U15.32
MN18+: U8.54, U16.9
MN18-: U8.52, U16.10
MN19+: U8.51, U16.13
MN19-: U8.49, U16.14
MN20+: U8.48, U16.31
MN20-: U8.47, U16.32
MN21+: U8.45, U17.9
MN21-: U8.44, U17.10
MN22+: U8.43, U17.13
MN22-: U8.42, U17.14
MN23+: U8.41, U17.31
MN23-: U8.40, U17.32
MN24+: U8.38, U18.9
MN24-: U8.37, U18.10
MN25+: U8.36, U18.13
MN25-: U8.34, U18.14
MN26+: U8.33, U18.31
MN26-: U8.31, U18.32
MODE: J1.d23, U120.3, U232.37, U233.28, U234.28, U235.9
MODEN: U231.37, U235.8
MWRH: U235.2, U240.43, U241.37, U242.43, U243.37, U244.43, U245.37, U287.1
N_K4: U52.9, U120.19
N_K5: U52.10, U120.20
N_K6: U53.9, U120.26
N_K7: U53.10, U120.27
N_K8: U54.9, U120.28
N_K9: U54.10, U120.29
N_V1: U27.9, U120.16
N_V2: U35.9, U120.17
N_V3: U43.9, U120.18
PB0: U302.8, U306.3
PB1: U303.12, U306.6
PB2: U303.6, U306.10
PB3: U303.8, U306.13
PB4: U304.12, U307.3
PB5: U304.6, U307.6
PB6: U304.8, U307.10
PB7: U305.12, U307.13
PM0: U300.12, U306.2
PM1: U300.6, U306.5
PM2: U300.8, U306.11
PM3: U301.12, U306.14
PM4: U301.6, U307.2
PM5: U301.8, U307.5
PM6: U302.12, U307.11
PM7: U302.6, U307.14
PRIV: J1.d25, U120.4
PROTEN: J1.d27, U120.5
PS0: U306.4, U308.3
PS1: U306.7, U308.4
PS2: U306.9, U308.5
PS3: U306.12, U308.6
PS4: U307.4, U308.7
PS5: U307.7, U308.16
PS6: U307.9, U308.17
PS7: U307.12, U308.18
RA0: U230.9, U240.5, U241.3, U242.5, U243.3, U244.5, U245.3, U258.3, U288.2
RA1: U230.10, U240.4, U241.4, U242.4, U243.4, U244.4, U245.4, U258.6, U288.5
RA2: U230.13, U240.3, U241.5, U242.3, U243.5, U244.3, U245.5, U258.10, U288.11
RA3: U230.14, U240.2, U241.6, U242.2, U243.6, U244.2, U245.6, U258.13, U288.14
RA4: U230.31, U240.1, U241.7, U242.1, U243.7, U244.1, U245.7, U259.3, U289.2
RA5: U230.32, U240.48, U241.16, U242.48, U243.16, U244.48, U245.16, U259.6, U289.5
RA6: U230.35, U240.47, U241.17, U242.47, U243.17, U244.47, U245.17, U259.10, U289.11
RA7: U230.36, U240.46, U241.18, U242.46, U243.18, U244.46, U245.18, U259.13, U289.14
RA8: U231.9, U232.9, U240.45, U241.19, U242.45, U243.19, U244.45, U245.19, U260.3, U290.2
RA9: U231.10, U232.10, U240.30, U241.20, U242.30, U243.20, U244.30, U245.20, U260.6, U290.5
RA10: U231.13, U232.13, U240.29, U241.26, U242.29, U243.26, U244.29, U245.26, U260.10, U290.11
RA11: U231.14, U232.14, U240.28, U241.27, U242.28, U243.27, U244.28, U245.27, U260.13, U290.14
RA12: U231.31, U232.31, U240.27, U241.28, U242.27, U243.28, U244.27, U245.28, U261.3, U291.2
RA13: U231.32, U232.32, U240.26, U241.29, U242.26, U243.29, U244.26, U245.29, U261.6, U291.5
RA14: U231.35, U232.35, U240.24, U241.30, U242.24, U243.30, U244.24, U245.30, U261.10, U291.11
RA15: U231.36, U232.36, U240.23, U241.38, U242.23, U243.38, U244.23, U245.38, U261.13, U291.14
RA16: U233.9, U240.22, U241.39, U242.22, U243.39, U244.22, U245.39, U262.3, U292.2
RA17: U233.10, U240.21, U241.40, U242.21, U243.40, U244.21, U245.40, U262.6, U292.5
RA18: U233.13, U240.20, U241.41, U242.20, U243.41, U244.20, U245.41, U262.10, U292.11
RA19: U233.14, U240.19, U241.25, U242.19, U243.25, U244.19, U245.25
RA20: U233.31, U240.44, U241.42, U242.44, U243.42, U244.44, U245.42
RAMD0: RN4.2, U240.8, U242.8, U244.8, U263.2, U277.18
RAMD1: RN4.3, U240.9, U242.9, U244.9, U263.5, U277.17
RAMD2: RN4.4, U240.10, U242.10, U244.10, U263.11, U277.16
RAMD3: RN4.5, U240.11, U242.11, U244.11, U263.14, U277.15
RAMD4: RN4.6, U240.14, U242.14, U244.14, U264.2, U277.14
RAMD5: RN4.7, U240.15, U242.15, U244.15, U264.5, U277.13
RAMD6: RN4.8, U240.16, U242.16, U244.16, U264.11, U277.12
RAMD7: RN4.9, U240.17, U242.17, U244.17, U264.14, U277.11
RAMD8: RN5.2, U240.31, U242.31, U244.31, U265.2, U278.18
RAMD9: RN5.3, U240.32, U242.32, U244.32, U265.5, U278.17
RAMD10: RN5.4, U240.33, U242.33, U244.33, U265.11, U278.16
RAMD11: RN5.5, U240.34, U242.34, U244.34, U265.14, U278.15
RAMD12: RN5.6, U240.37, U242.37, U244.37, U266.2, U278.14
RAMD13: RN5.7, U240.38, U242.38, U244.38, U266.5, U278.13
RAMD14: RN5.8, U240.39, U242.39, U244.39, U266.11, U278.12
RAMD15: RN5.9, U240.40, U242.40, U244.40, U266.14, U278.11
RAMD16: RN6.2, U241.9, U243.9, U245.9, U267.2, U279.18
RAMD17: RN6.3, U241.10, U243.10, U245.10, U267.5, U279.17
RD0: U161.3, U170.3, U179.3, U191.3, U263.4
RD1: U161.13, U170.13, U179.13, U191.13, U263.7
RD2: U162.3, U171.3, U180.3, U192.3, U263.9
RD3: U162.13, U171.13, U180.13, U192.13, U263.12
RD4: U163.3, U172.3, U181.3, U193.3, U264.4
RD5: U163.13, U172.13, U181.13, U193.13, U264.7
RD6: U164.3, U173.3, U182.3, U194.3, U264.9
RD7: U164.13, U173.13, U182.13, U194.13, U264.12
RD8: U165.3, U174.3, U183.3, U195.3, U265.4
RD9: U165.13, U174.13, U183.13, U195.13, U265.7
RD10: U166.3, U175.3, U184.3, U196.3, U265.9
RD11: U166.13, U175.13, U184.13, U196.13, U265.12
RD12: U167.3, U176.3, U185.3, U197.3, U266.4
RD13: U167.13, U176.13, U185.13, U197.13, U266.7
RD14: U168.3, U177.3, U186.3, U198.3, U266.9
RD15: U168.13, U177.13, U186.13, U198.13, U266.12
RD16: U169.3, U178.3, U187.3, U199.3, U267.4
RD17: U169.13, U178.13, U187.13, U199.13, U267.7
RESET: J1.c12, U4.2, U4.27, U5.2, U5.27
RSLOT0: J1.d11, U122.3
RSLOT1: J1.d12, U122.4
RSLOT2: J1.d13, U122.5
RSLOT3: J1.d14, U122.6
RSLOT4: J1.d15, U122.7
SA0: U258.2, U288.3
SA1: U258.5, U288.6
SA2: U258.11, U288.10
SA3: U258.14, U288.13
SA4: U259.2, U289.3
SA5: U259.5, U289.6
SA6: U259.11, U289.10
SA7: U259.14, U289.13
SA8: U260.2, U290.3
SA9: U260.5, U290.6
SA10: U260.11, U290.10
SA11: U260.14, U290.13
SA12: U261.2, U291.3
SA13: U261.5, U291.6
SA14: U261.11, U291.10
SA15: U261.14, U291.13
SA16: U262.2, U292.3
SA17: U262.5, U292.6
SA18: U262.11, U292.10
SCLK: J1.c11, U284.11, U285.11
SD0: U257.7, U282.18, U284.2, U295.18
SD1: U257.8, U282.17, U284.3, U295.17
SD2: U257.9, U282.16, U284.4, U295.16
SD3: U257.10, U282.15, U284.5, U295.15
SD4: U257.13, U282.14, U284.6, U295.14
SD5: U257.14, U282.13, U284.7, U295.13
SD6: U257.15, U282.12, U284.8, U295.12
SD7: U257.16, U282.11, U284.9, U295.11
SD8: U257.29, U283.18, U285.2, U296.18
SD9: U257.30, U283.17, U285.3, U296.17
SD10: U257.31, U283.16, U285.4, U296.16
SD11: U257.32, U283.15, U285.5, U296.15
SI0: U293.2, U295.2
SI1: U293.3, U295.3
SI2: U293.4, U295.4
SI3: U293.5, U295.5
SI4: U293.6, U295.6
SI5: U293.7, U295.7
SI6: U293.8, U295.8
SI7: U293.9, U295.9
SI8: U294.2, U296.2
SI9: U294.3, U296.3
SI10: U294.4, U296.4
SI11: U294.5, U296.5
SPRNR: J1.c18, U122.17
SWRH: U235.10, U287.2, U287.5, U288.1, U289.1, U290.1, U291.1, U292.1
UA0: J1.b30, U1.3, U2.3, U3.3
UA1: J1.b31, U1.4, U2.4, U3.4
UA2: J1.c1, U1.5, U2.5, U3.5
UA3: J1.c2, U1.6, U2.6, U3.6
UA4: J1.c3, U1.7, U2.7, U3.7
UA5: J1.c4, U1.16, U2.16, U3.16
UA6: J1.c5, U1.17, U2.17, U3.17
UA7: J1.c6, U1.18, U2.18, U3.18
UA8: J1.c7, U1.19, U2.19, U3.19
UA9: J1.c9, U1.20, U2.20, U3.20
UB0+: U20.19, U123.3
UB0-: U20.20, U123.5
UB1+: U20.26, U123.6
UB1-: U20.27, U123.8
UB2+: U20.28, U123.9
UB2-: U20.29, U123.10
UB3+: U20.30, U123.12
UB3-: U20.38, U123.13
UB4+: U21.19, U123.14
UB4-: U21.20, U123.15
UB5+: U21.26, U123.16
UB5-: U21.27, U123.17
UB6+: U21.28, U123.19
UB6-: U21.29, U123.20
UB7+: U21.30, U123.21
UB7-: U21.38, U123.23
UB8+: U22.19, U123.24
UB8-: U22.20, U123.26
UB9+: U22.26, U124.3
UB9-: U22.27, U124.5
UB10+: U22.28, U124.6
UB10-: U22.29, U124.8
UB11+: U22.30, U124.9
UB11-: U22.38, U124.10
UB12+: U23.19, U124.12
UB12-: U23.20, U124.13
UB13+: U23.26, U124.14
UB13-: U23.27, U124.15
UB14+: U23.28, U124.16
UB14-: U23.29, U124.17
UB15+: U23.30, U124.19
UB15-: U23.38, U124.20
UB16+: U24.19, U124.21
UB16-: U24.20, U124.23
UB17+: U24.26, U124.24
UB17-: U24.27, U124.26
UB18+: U24.28, U125.3
UB18-: U24.29, U125.5
UB19+: U24.30, U125.6
UB19-: U24.38, U125.8
UB20+: U25.19, U125.9
UB20-: U25.20, U125.10
UB21+: U25.26, U125.12
UB21-: U25.27, U125.13
UB22+: U25.28, U125.14
UB22-: U25.29, U125.15
UB23+: U25.30, U125.16
UB23-: U25.38, U125.17
UB24+: U26.19, U125.19
UB24-: U26.20, U125.20
UB25+: U26.26, U125.21
UB25-: U26.27, U125.23
UB26+: U26.28, U125.24
UB26-: U26.29, U125.26
UL0+: U28.19, U126.3, U130.5
UL0-: U28.20, U126.5, U130.11
UL1+: U28.26, U126.6, U131.5
UL1-: U28.27, U126.8, U131.11
UL2+: U28.28, U126.9, U132.5
UL2-: U28.29, U126.10, U132.11
UL2UF: U43.30, U326.3
UL2UFN: U312.8, U326.54
UL3+: U28.30, U126.12, U133.5
UL3-: U28.38, U126.13, U133.11
UL4+: U29.19, U126.14, U134.5
UL4-: U29.20, U126.15, U134.11
UL5+: U29.26, U126.16, U135.5
UL5-: U29.27, U126.17, U135.11
UL6+: U29.28, U126.19, U136.5
UL6-: U29.29, U126.20, U136.11
UL7+: U29.30, U126.21, U137.5
UL7-: U29.38, U126.23, U137.11
UL8+: U30.19, U126.24, U138.5
UL8-: U30.20, U126.26, U138.11
UL9+: U30.26, U127.3, U139.5
UL9-: U30.27, U127.5, U139.11
UL10+: U30.28, U127.6, U140.5
UL10-: U30.29, U127.8, U140.11
UL11+: U30.30, U127.9, U141.5
UL11-: U30.38, U127.10, U141.11
UL12+: U31.19, U127.12, U142.5
UL12-: U31.20, U127.13, U142.11
UL13+: U31.26, U127.14, U143.5
UL13-: U31.27, U127.15, U143.11
UL14+: U31.28, U127.16, U144.5
UL14-: U31.29, U127.17, U144.11
UL15+: U31.30, U127.19, U145.5
UL15-: U31.38, U127.20, U145.11
UL16+: U32.19, U127.21, U146.5
UL16-: U32.20, U127.23, U146.11
UL17+: U32.26, U127.24, U147.5
UL17-: U32.27, U127.26, U147.11
UL18+: U32.28, U128.3, U148.5
UL18-: U32.29, U128.5, U148.11
UL19+: U32.30, U128.6, U149.5
UL19-: U32.38, U128.8, U149.11
UL20+: U33.19, U128.9, U150.5
UL20-: U33.20, U128.10, U150.11
UL21+: U33.26, U128.12, U151.5
UL21-: U33.27, U128.13, U151.11
UL22+: U33.28, U128.14, U152.5
UL22-: U33.29, U128.15, U152.11
UL23+: U33.30, U128.16, U153.5
UL23-: U33.38, U128.17, U153.11
UL24+: U34.19, U128.19, U154.5
UL24-: U34.20, U128.20, U154.11
UL25+: U34.26, U128.21, U155.5
UL25-: U34.27, U128.23, U155.11
UL26+: U34.28, U128.24, U156.5
UL26-: U34.29, U128.26, U156.11
ULM0+: U36.19, U323.3
ULM0-: U36.20, U323.5
ULM1+: U36.26, U323.6
ULM1-: U36.27, U323.8
ULM2+: U36.28, U323.9
ULM2-: U36.29, U323.10
ULM3+: U36.30, U323.12
ULM3-: U36.38, U323.13
ULM4+: U37.19, U323.14
ULM4-: U37.20, U323.15
ULM5+: U37.26, U323.16
ULM5-: U37.27, U323.17
ULM6+: U37.28, U323.19
ULM6-: U37.29, U323.20
ULM7+: U37.30, U323.21
ULM7-: U37.38, U323.23
ULM8+: U38.19, U323.24
ULM8-: U38.20, U323.26
ULM9+: U38.26, U324.3
ULM9-: U38.27, U324.5
ULM10+: U38.28, U324.6
ULM10-: U38.29, U324.8
ULM11+: U38.30, U324.9
ULM11-: U38.38, U324.10
ULM12+: U39.19, U324.12
ULM12-: U39.20, U324.13
ULM13+: U39.26, U324.14
ULM13-: U39.27, U324.15
ULM14+: U39.28, U324.16
ULM14-: U39.29, U324.17
ULM15+: U39.30, U324.19
ULM15-: U39.38, U324.20
ULM16+: U40.19, U324.21
ULM16-: U40.20, U324.23
ULM17+: U40.26, U324.24
ULM17-: U40.27, U324.26
ULM18+: U40.28, U325.3
ULM18-: U40.29, U325.5
ULM19+: U40.30, U325.6
ULM19-: U40.38, U325.8
ULM20+: U41.19, U325.9
ULM20-: U41.20, U325.10
ULM21+: U41.26, U325.12
ULM21-: U41.27, U325.13
ULM22+: U41.28, U325.14
ULM22-: U41.29, U325.15
ULM23+: U41.30, U325.16
ULM23-: U41.38, U325.17
ULM24+: U42.19, U325.19
ULM24-: U42.20, U325.20
ULM25+: U42.26, U325.21
ULM25-: U42.27, U325.23
ULM26+: U42.28, U325.24
ULM26-: U42.29, U325.26
V1s0+: U20.9, U27.3
V1s0-: U20.10, U27.4
V1s1+: U21.9, U27.5
V1s1-: U21.10, U27.6
V1s2+: U22.9, U27.7
V1s2-: U22.10, U27.16
V1s3+: U23.9, U27.17
V1s3-: U23.10, U27.18
V1s4+: U24.9, U27.19
V1s4-: U24.10, U27.20
V1s5+: U25.9, U27.26
V1s5-: U25.10, U27.27
V1s6+: U26.9, U27.28
V1s6-: U26.10, U27.29
V2s0+: U28.9, U35.3
V2s0-: U28.10, U35.4
V2s1+: U29.9, U35.5
V2s1-: U29.10, U35.6
V2s2+: U30.9, U35.7
V2s2-: U30.10, U35.16
V2s3+: U31.9, U35.17
V2s3-: U31.10, U35.18
V2s4+: U32.9, U35.19
V2s4-: U32.10, U35.20
V2s5+: U33.9, U35.26
V2s5-: U33.10, U35.27
V2s6+: U34.9, U35.28
V2s6-: U34.10, U35.29
V3s0+: U36.9, U43.3
V3s0-: U36.10, U43.4
V3s1+: U37.9, U43.5
V3s1-: U37.10, U43.6
V3s2+: U38.9, U43.7
V3s2-: U38.10, U43.16
V3s3+: U39.9, U43.17
V3s3-: U39.10, U43.18
V3s4+: U40.9, U43.19
V3s4-: U40.10, U43.20
V3s5+: U41.9, U43.26
V3s5-: U41.10, U43.27
V3s6+: U42.9, U43.28
V3s6-: U42.10, U43.29
VBUSY: U235.4, U258.1, U259.1, U260.1, U261.1, U262.1, U287.4
VCA0: U256.1, U288.4
VCA1: U256.2, U288.7
VCA2: U256.3, U288.9
VCA3: U256.4, U288.12
VCA4: U256.5, U289.4
VCA5: U256.18, U289.7
VCA6: U256.19, U289.9
VCA7: U256.20, U289.12
VCA8: U256.21, U290.4
VCA9: U256.22, U290.7
VCA10: U256.23, U290.9
VCA11: U256.24, U290.12
VCA12: U256.25, U291.4
VCA13: U256.26, U291.7
VCA14: U256.27, U291.9
VCA15: U256.42, U291.12
VCA16: U256.43, U292.4
VCA17: U256.44, U292.7
VCA18: U256.28, U292.9
VCOE: U256.41, U287.3
VD0: U256.7, U263.3, U280.18, U293.18
VD1: U256.8, U263.6, U280.17, U293.17
VD2: U256.9, U263.10, U280.16, U293.16
VD3: U256.10, U263.13, U280.15, U293.15
VD4: U256.13, U264.3, U280.14, U293.14
VD5: U256.14, U264.6, U280.13, U293.13
VD6: U256.15, U264.10, U280.12, U293.12
VD7: U256.16, U264.13, U280.11, U293.11
VD8: U256.29, U265.3, U281.18, U294.18
VD9: U256.30, U265.6, U281.17, U294.17
VD10: U256.31, U265.10, U281.16, U294.16
VD11: U256.32, U265.13, U281.15, U294.15
VSA0: U257.1, U258.4
VSA1: U257.2, U258.7
VSA2: U257.3, U258.9
VSA3: U257.4, U258.12
VSA4: U257.5, U259.4
VSA5: U257.18, U259.7
VSA6: U257.19, U259.9
VSA7: U257.20, U259.12
VSA8: U257.21, U260.4
VSA9: U257.22, U260.7
VSA10: U257.23, U260.9
VSA11: U257.24, U260.12
VSA12: U257.25, U261.4
VSA13: U257.26, U261.7
VSA14: U257.27, U261.9
VSA15: U257.42, U261.12
VSA16: U257.43, U262.4
VSA17: U257.44, U262.7
VSA18: U257.28, U262.9
VSOE: U257.41, U287.6
WD0: U268.7, U277.2, U280.2, U282.2
WD1: U268.9, U277.3, U280.3, U282.3
WD2: U269.7, U277.4, U280.4, U282.4
WD3: U269.9, U277.5, U280.5, U282.5
WD4: U270.7, U277.6, U280.6, U282.6
WD5: U270.9, U277.7, U280.7, U282.7
WD6: U271.7, U277.8, U280.8, U282.8
WD7: U271.9, U277.9, U280.9, U282.9
WD8: U272.7, U278.2, U281.2, U283.2
WD9: U272.9, U278.3, U281.3, U283.3
WD10: U273.7, U278.4, U281.4, U283.4
WD11: U273.9, U278.5, U281.5, U283.5
WD12: U274.7, U278.6
WD13: U274.9, U278.7
WD14: U275.7, U278.8
WD15: U275.9, U278.9
WD16: U276.7, U279.2
WD17: U276.9, U279.3
